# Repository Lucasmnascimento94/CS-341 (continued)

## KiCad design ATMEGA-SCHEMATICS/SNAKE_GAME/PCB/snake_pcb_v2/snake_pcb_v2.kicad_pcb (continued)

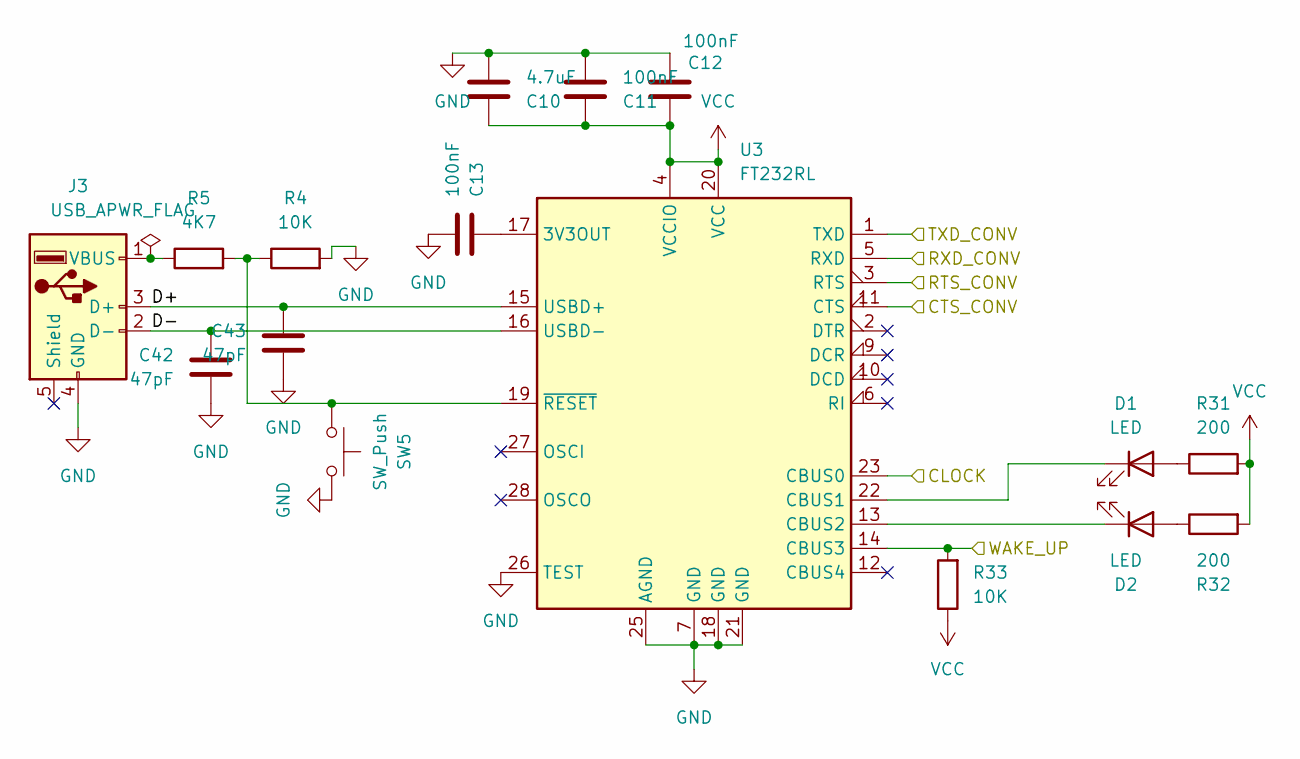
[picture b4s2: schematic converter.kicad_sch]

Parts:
C10: 4.7uF; C_0805_2012Metric
C11, C12, C13: 100nF; C_0402_1005Metric
C42, C43: 47pF; C_0402_1005Metric
D1, D2: LED; LED_0603_1608Metric
J3: USB_A; USB_B_Lumberg_2411_02_Horizontal
R4, R33: 10K; R_0402_1005Metric
R5: 4K7; R_0402_1005Metric
R31, R32: 200; R_0402_1005Metric
SW5: SW_Push; SW_PUSH_1P1T_6x3.5mm_H4.3_APEM_MJTP1243
U3: FT232RL; SSOP-28_5.3x10.2mm_P0.65mm

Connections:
/converter/CLOCK: U3.23 (CBUS0); also elsewhere on the board
/converter/CTS_CONV: U3.11 (CTS); also elsewhere on the board
/converter/D+: C43.1, J3.3 (D+), U3.15 (USBD+)
/converter/D-: C42.1, J3.2 (D-), U3.16 (USBD-)
/converter/RTS_CONV: U3.3 (RTS); also elsewhere on the board
/converter/RXD_CONV: U3.5 (RXD); also elsewhere on the board
/converter/TXD_CONV: U3.1 (TXD); also elsewhere on the board
/converter/WAKE_UP: R33.2, U3.14 (CBUS3); also elsewhere on the board
GND: C10.2, C11.2, C12.2, C13.2, C42.2, C43.2, J3.4 (GND), R4.2, SW5.2, U3.7 (GND), U3.18 (GND), U3.21 (GND), U3.25 (AGND), U3.26 (TEST); also elsewhere on the board
unnamed: D1.2 (A), R31.1
unnamed: D1.1 (K), U3.22 (CBUS1)
unnamed: D2.2 (A), R32.1
unnamed: D2.1 (K), U3.13 (CBUS2)
unnamed: J3.1 (VBUS), R5.1
unnamed: C13.1, U3.17 (3V3OUT)
unnamed: R4.1, R5.2, SW5.1, U3.19 (~RESET)
VCC: C10.1, C11.1, C12.1, R31.2, R32.2, R33.1, U3.4 (VCCIO), U3.20 (VCC); also elsewhere on the board

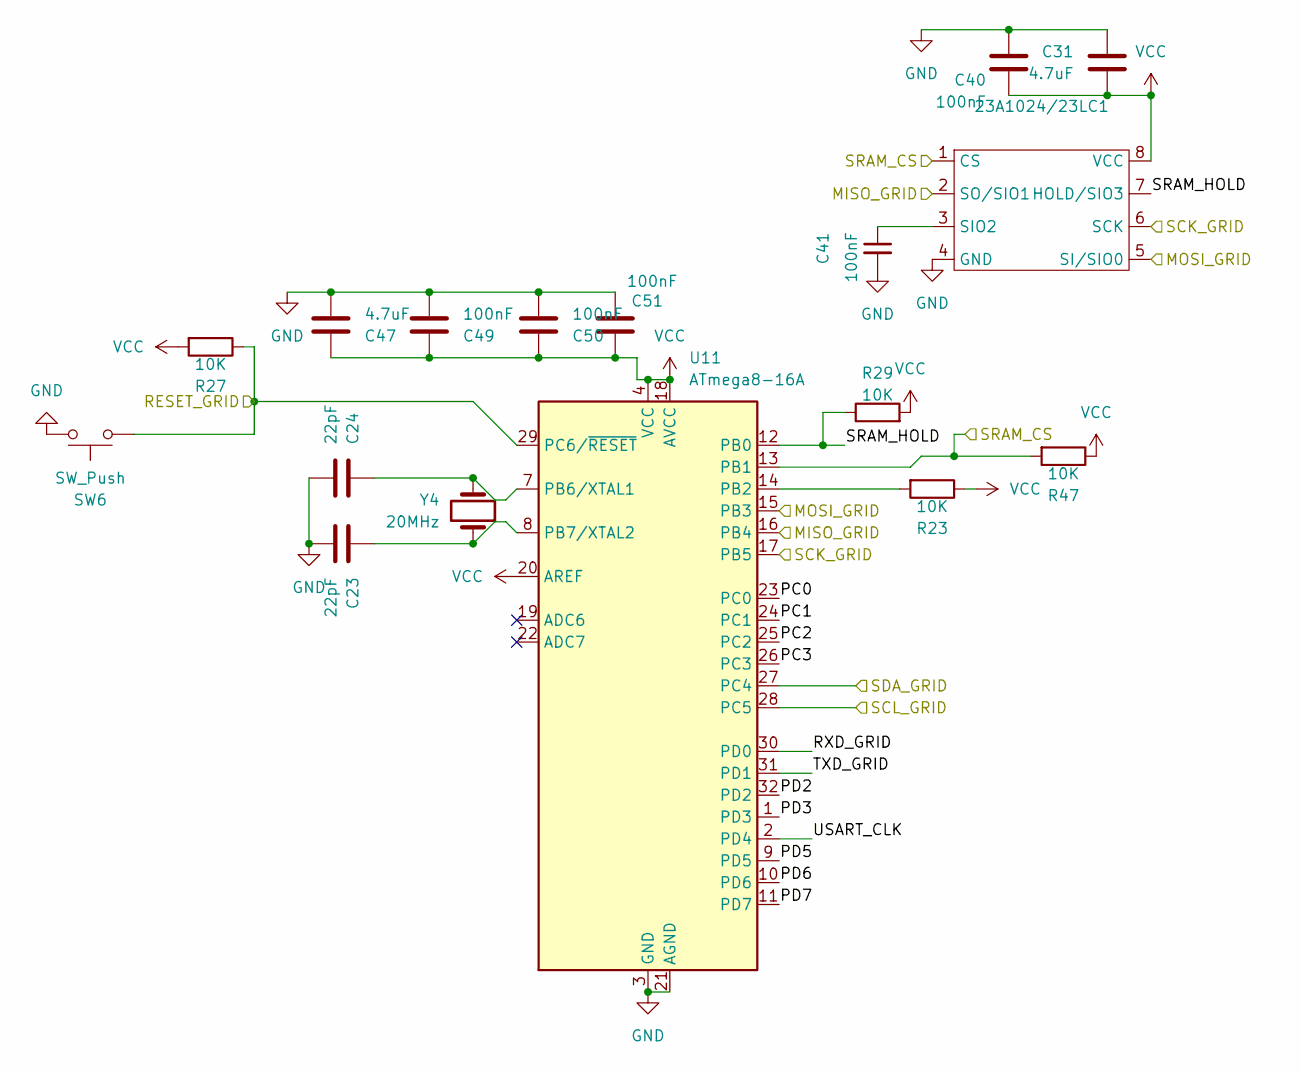
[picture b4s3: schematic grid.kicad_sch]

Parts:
23A1024/23LC1: JEITA_SOIC-8_3.9x4.9mm_P1.27mm
C23, C24: 22pF; C_0402_1005Metric
C31, C47: 4.7uF; C_0805_2012Metric
C40, C41, C49, C50, C51: 100nF; C_0402_1005Metric
R23, R27, R29, R47: 10K; R_0402_1005Metric
SW6: SW_Push; SW_PUSH_1P1T_6x3.5mm_H4.3_APEM_MJTP1243
U11: ATmega8-16A; TQFP-32_7x7mm_P0.8mm
Y4: 20MHz; Crystal_SMD_3225-4Pin_3.2x2.5mm_HandSoldering

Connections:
/game/SCL_GAME: U11.28 (PC5); also elsewhere on the board
/game/SDA_GAME: U11.27 (PC4); also elsewhere on the board
/grid/MISO_GRID: 23A1024/23LC1.2 (SO/SIO1), U11.16 (PB4); also elsewhere on the board
/grid/MOSI_GRID: 23A1024/23LC1.5 (SI/SIO0), U11.15 (PB3); also elsewhere on the board
/grid/PC0: U11.23 (PC0)
/grid/PC1: U11.24 (PC1)
/grid/PC2: U11.25 (PC2)
/grid/PC3: U11.26 (PC3)
/grid/PD2: U11.32 (PD2)
/grid/PD3: U11.1 (PD3)
/grid/PD5: U11.9 (PD5)
/grid/PD6: U11.10 (PD6)
/grid/PD7: U11.11 (PD7)
/grid/RESET_GRID: R27.1, SW6.1, U11.29 (PC6/~RESET); also elsewhere on the board
/grid/RXD_GRID: U11.30 (PD0)
/grid/SCK_GRID: 23A1024/23LC1.6 (SCK), U11.17 (PB5); also elsewhere on the board
/grid/SRAM_CS: 23A1024/23LC1.1 (CS), R47.2, U11.13 (PB1); also elsewhere on the board
/grid/SRAM_HOLD: 23A1024/23LC1.7 (HOLD/SIO3), R29.1, U11.12 (PB0)
/grid/TXD_GRID: U11.31 (PD1)
/grid/USART_CLK: U11.2 (PD4)
GND: 23A1024/23LC1.4 (GND), C23.2, C24.2, C31.1, C40.1, C41.2, C47.2, C49.2, C50.2, C51.2, SW6.2, U11.3 (GND), U11.5 (GND), U11.21 (AGND); also elsewhere on the board
unnamed: 23A1024/23LC1.3 (SIO2), C41.1
unnamed: R23.2, U11.14 (PB2)
unnamed: C24.1, U11.7 (PB6/XTAL1), Y4.2
unnamed: C23.1, U11.8 (PB7/XTAL2), Y4.1
VCC: 23A1024/23LC1.8 (VCC), C31.2, C40.2, C47.1, C49.1, C50.1, C51.1, R23.1, R27.2, R29.2, R47.1, U11.4 (VCC), U11.6 (VCC), U11.18 (AVCC), U11.20 (AREF); also elsewhere on the board

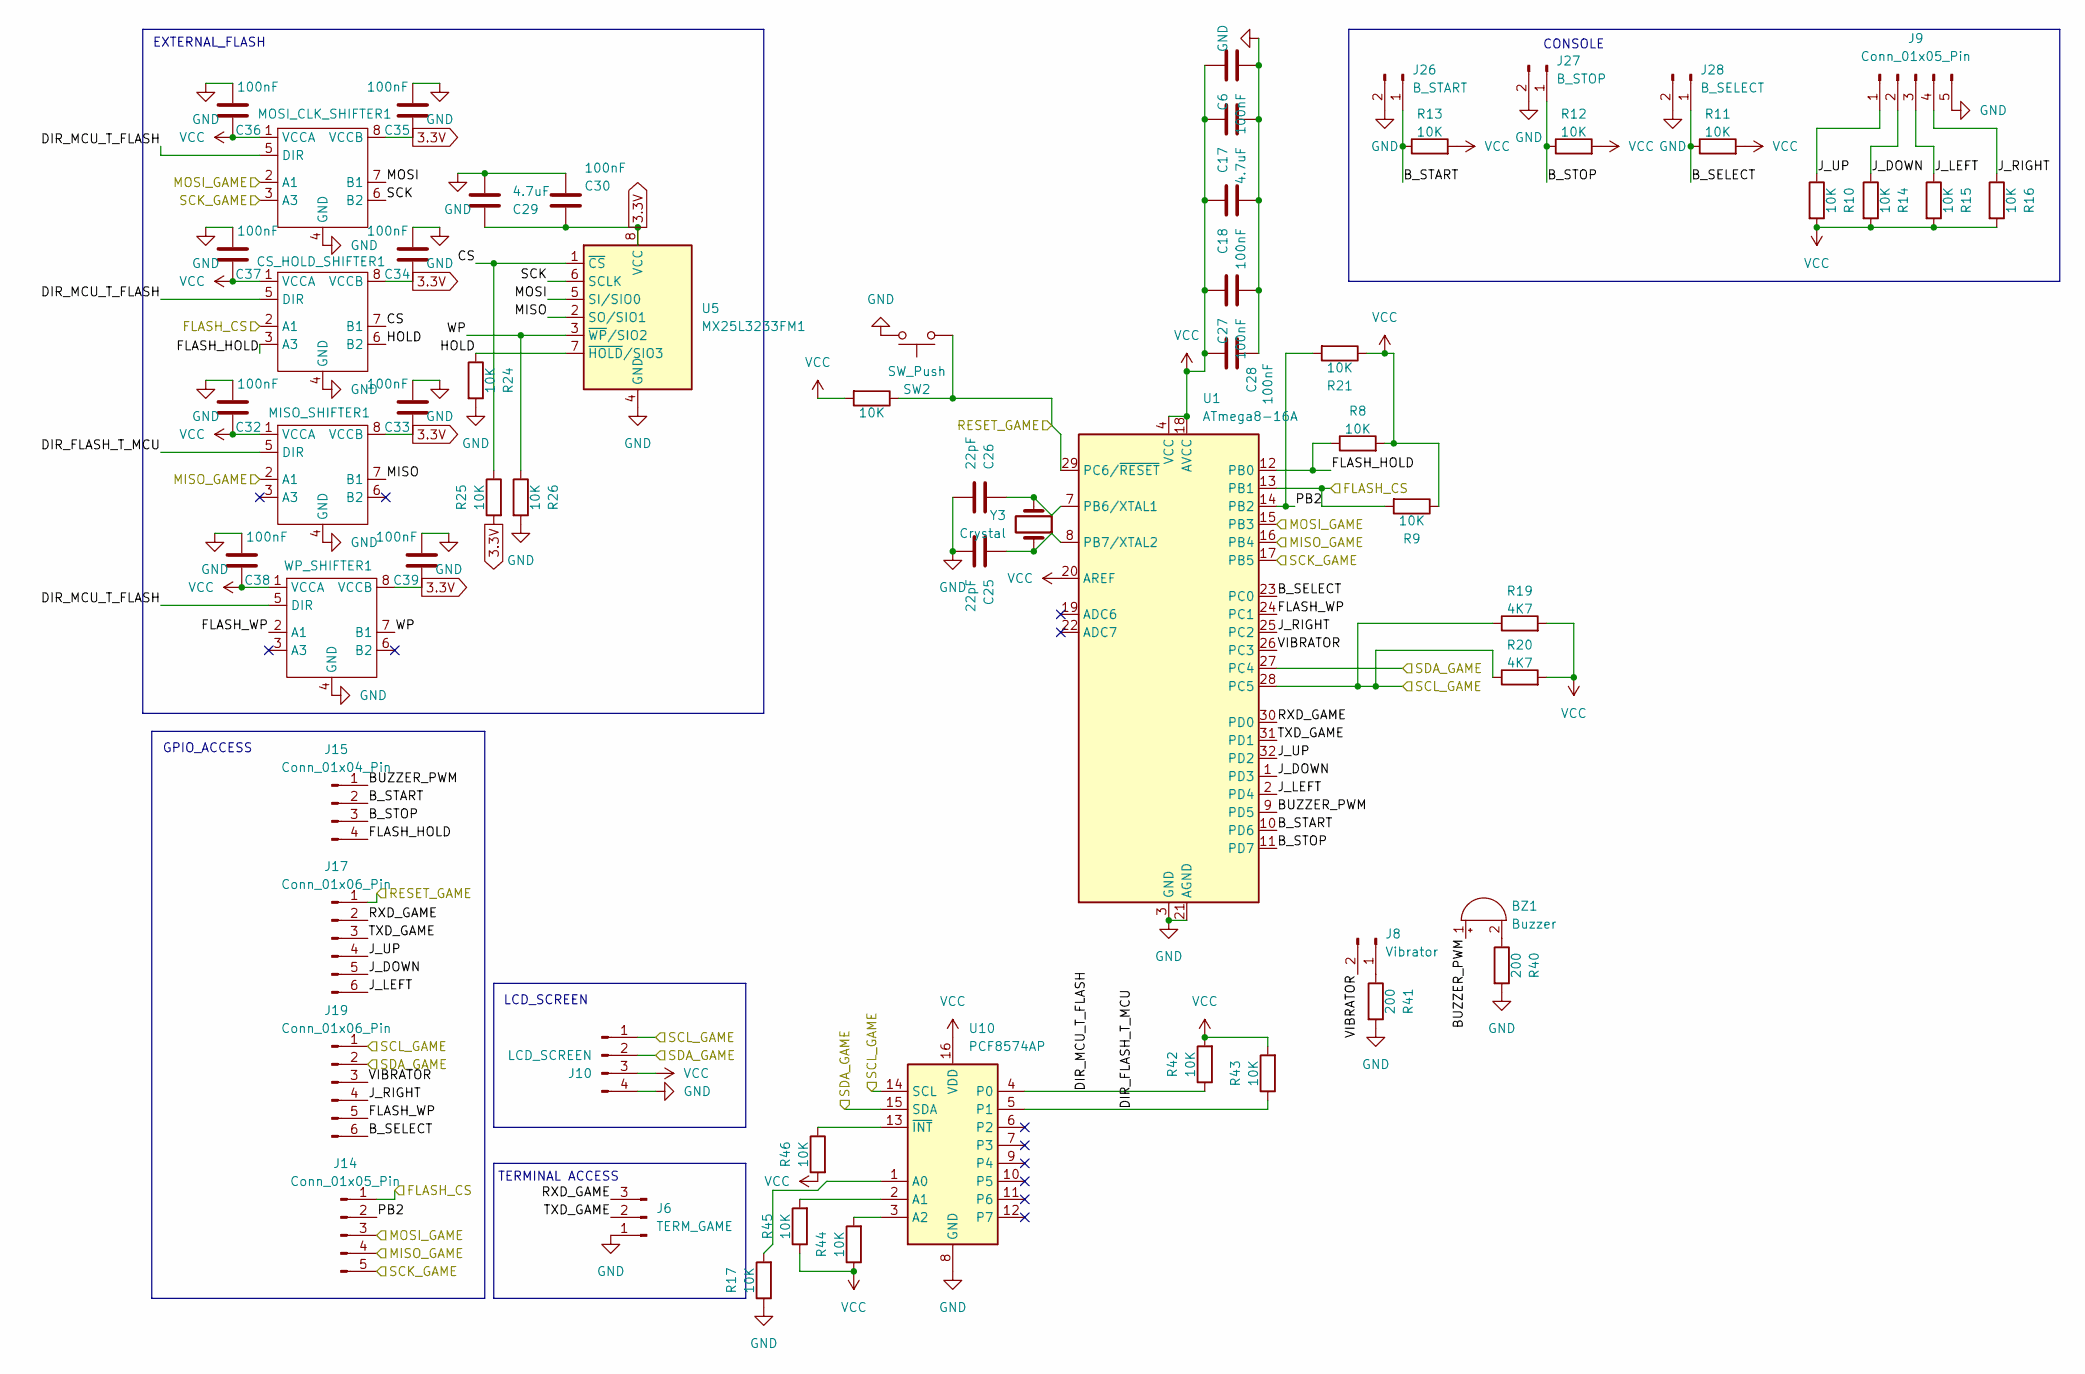
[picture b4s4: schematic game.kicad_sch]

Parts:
BZ1: Buzzer; Buzzer_12x9.5RM7.6
C6, C18, C27, C28, C30, C32, C33, C34, C35, C36, C37, C38, C39: 100nF; C_0402_1005Metric
C17, C29: 4.7uF; C_0805_2012Metric
C25, C26: 22pF; C_0402_1005Metric
CS_HOLD_SHIFTER1: DIP-8_W7.62mm
J6: TERM_GAME; PinSocket_1x03_P2.54mm_Vertical
J8: Vibrator; PinHeader_1x02_P2.54mm_Vertical
J9: Conn_01x05_Pin; PinSocket_1x05_P2.54mm_Vertical
J10: LCD_SCREEN; PinSocket_1x04_P2.54mm_Vertical
J14: Conn_01x05_Pin; PinHeader_1x05_P2.54mm_Vertical
J15: Conn_01x04_Pin; PinHeader_1x04_P2.54mm_Vertical
J17, J19: Conn_01x06_Pin; PinHeader_1x06_P2.54mm_Vertical
J26: B_START; PinHeader_1x02_P2.54mm_Vertical
J27: B_STOP; PinHeader_1x02_P2.54mm_Vertical
J28: B_SELECT; PinHeader_1x02_P2.54mm_Vertical
MISO_SHIFTER1: DIP-8_W7.62mm
MOSI_CLK_SHIFTER1: DIP-8_W7.62mm
R7, R8, R9, R10, R11, R12, R13, R14, R15, R16, R17, R21, R24, R25, R26, R42, R43, R44, R45, R46: 10K; R_0402_1005Metric
R19, R20: 4K7; R_0402_1005Metric
R40, R41: 200; R_0402_1005Metric
SW2: SW_Push; SW_PUSH_1P1T_6x3.5mm_H4.3_APEM_MJTP1243
U1: ATmega8-16A; TQFP-32_7x7mm_P0.8mm
U5: MX25L3233FM1; JEITA_SOIC-8_3.9x4.9mm_P1.27mm
U10: PCF8574AP; DIP-16_W7.62mm
WP_SHIFTER1: DIP-8_W7.62mm
Y3: Crystal; Crystal_SMD_3225-4Pin_3.2x2.5mm_HandSoldering

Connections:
3.3V: C29.1, C30.1, C33.1, C34.1, C35.1, C39.1, CS_HOLD_SHIFTER1.8 (VCCB), MISO_SHIFTER1.8 (VCCB), MOSI_CLK_SHIFTER1.8 (VCCB), R25.2, U5.8 (VCC), WP_SHIFTER1.8 (VCCB); also elsewhere on the board
/game/BUZZER_PWM: BZ1.1 (+), J15.1, U1.9 (PD5)
/game/B_SELECT: J19.6, J28.1, R11.1, U1.23 (PC0)
/game/B_START: J15.2, J26.1, R13.1, U1.10 (PD6)
/game/B_STOP: J15.3, J27.1, R12.1, U1.11 (PD7)
/game/CS: CS_HOLD_SHIFTER1.7 (B1), R25.1, U5.1 (~CS)
/game/DIR_FLASH_T_MCU: MISO_SHIFTER1.5 (DIR), R43.1, U10.5 (P1)
/game/DIR_MCU_T_FLASH: CS_HOLD_SHIFTER1.5 (DIR), MOSI_CLK_SHIFTER1.5 (DIR), R42.1, U10.4 (P0), WP_SHIFTER1.5 (DIR)
/game/FLASH_CS: CS_HOLD_SHIFTER1.2 (A1), J14.1, R9.2, U1.13 (PB1); also elsewhere on the board
/game/FLASH_HOLD: CS_HOLD_SHIFTER1.3 (A3), J15.4, R8.1, U1.12 (PB0)
/game/FLASH_WP: J19.5, U1.24 (PC1), WP_SHIFTER1.2 (A1)
/game/HOLD: CS_HOLD_SHIFTER1.6 (B2), R24.1, U5.7 (~HOLD/SIO3)
/game/J_DOWN: J9.2, J17.5, R14.1, U1.1 (PD3)
/game/J_LEFT: J9.3, J17.6, R15.1, U1.2 (PD4)
/game/J_RIGHT: J9.4, J19.4, R16.1, U1.25 (PC2)
/game/J_UP: J9.1, J17.4, R10.1, U1.32 (PD2)
/game/MISO: MISO_SHIFTER1.7 (B1), U5.2 (SO/SIO1)
/game/MISO_GAME: J14.4, MISO_SHIFTER1.2 (A1), U1.16 (PB4); also elsewhere on the board
/game/MOSI: MOSI_CLK_SHIFTER1.7 (B1), U5.5 (SI/SIO0)
/game/MOSI_GAME: J14.3, MOSI_CLK_SHIFTER1.2 (A1), U1.15 (PB3); also elsewhere on the board
/game/PB2: J14.2, R21.2, U1.14 (PB2)
/game/RESET_GAME: J17.1, R7.1, SW2.1, U1.29 (PC6/~RESET); also elsewhere on the board
/game/RXD_GAME: J6.3, J17.2, U1.30 (PD0)
/game/SCK: MOSI_CLK_SHIFTER1.6 (B2), U5.6 (SCLK)
/game/SCK_GAME: J14.5, MOSI_CLK_SHIFTER1.3 (A3), U1.17 (PB5); also elsewhere on the board
/game/SCL_GAME: J10.1, J19.1, R19.1, R20.1, U1.28 (PC5), U10.14 (SCL); also elsewhere on the board
/game/SDA_GAME: J10.2, J19.2, U1.27 (PC4), U10.15 (SDA); also elsewhere on the board
/game/TXD_GAME: J6.2, J17.3, U1.31 (PD1)
/game/VIBRATOR: J8.2, J19.3, U1.26 (PC3)
/game/WP: R26.1, U5.3 (~WP/SIO2), WP_SHIFTER1.7 (B1)
GND: C6.2, C17.2, C18.2, C25.2, C26.2, C27.2, C28.2, C29.2, C30.2, C32.2, C33.2, C34.2, C35.2, C36.2, C37.2, C38.2, C39.2, CS_HOLD_SHIFTER1.4 (GND), J6.1, J9.5, J10.4, J26.2, J27.2, J28.2, MISO_SHIFTER1.4 (GND), MOSI_CLK_SHIFTER1.4 (GND), R17.1, R24.2, R26.2, R40.2, R41.2, SW2.2, U1.3 (GND), U1.5 (GND), U1.21 (AGND), U5.4 (GND), U10.8 (GND), WP_SHIFTER1.4 (GND); also elsewhere on the board
unnamed: BZ1.2 (-), R40.1
unnamed: J8.1, R41.1
unnamed: C26.1, U1.7 (PB6/XTAL1), Y3.2
unnamed: C25.1, U1.8 (PB7/XTAL2), Y3.1
unnamed: R17.2, U10.1 (A0)
unnamed: R45.2, U10.2 (A1)
unnamed: R44.2, U10.3 (A2)
unnamed: R46.1, U10.13 (~INT)
VCC: C6.1, C17.1, C18.1, C27.1, C28.1, C32.1, C36.1, C37.1, C38.1, CS_HOLD_SHIFTER1.1 (VCCA), J10.3, MISO_SHIFTER1.1 (VCCA), MOSI_CLK_SHIFTER1.1 (VCCA), R7.2, R8.2, R9.1, R10.2, R11.2, R12.2, R13.2, R14.2, R15.2, R16.2, R19.2, R20.2, R21.1, R42.2, R43.2, R44.1, R45.1, R46.2, U1.4 (VCC), U1.6 (VCC), U1.18 (AVCC), U1.20 (AREF), U10.16 (VDD), WP_SHIFTER1.1 (VCCA); also elsewhere on the board

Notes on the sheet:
TERMINAL ACCESS
GPIO_ACCESS
CONSOLE
EXTERNAL_FLASH
LCD_SCREEN

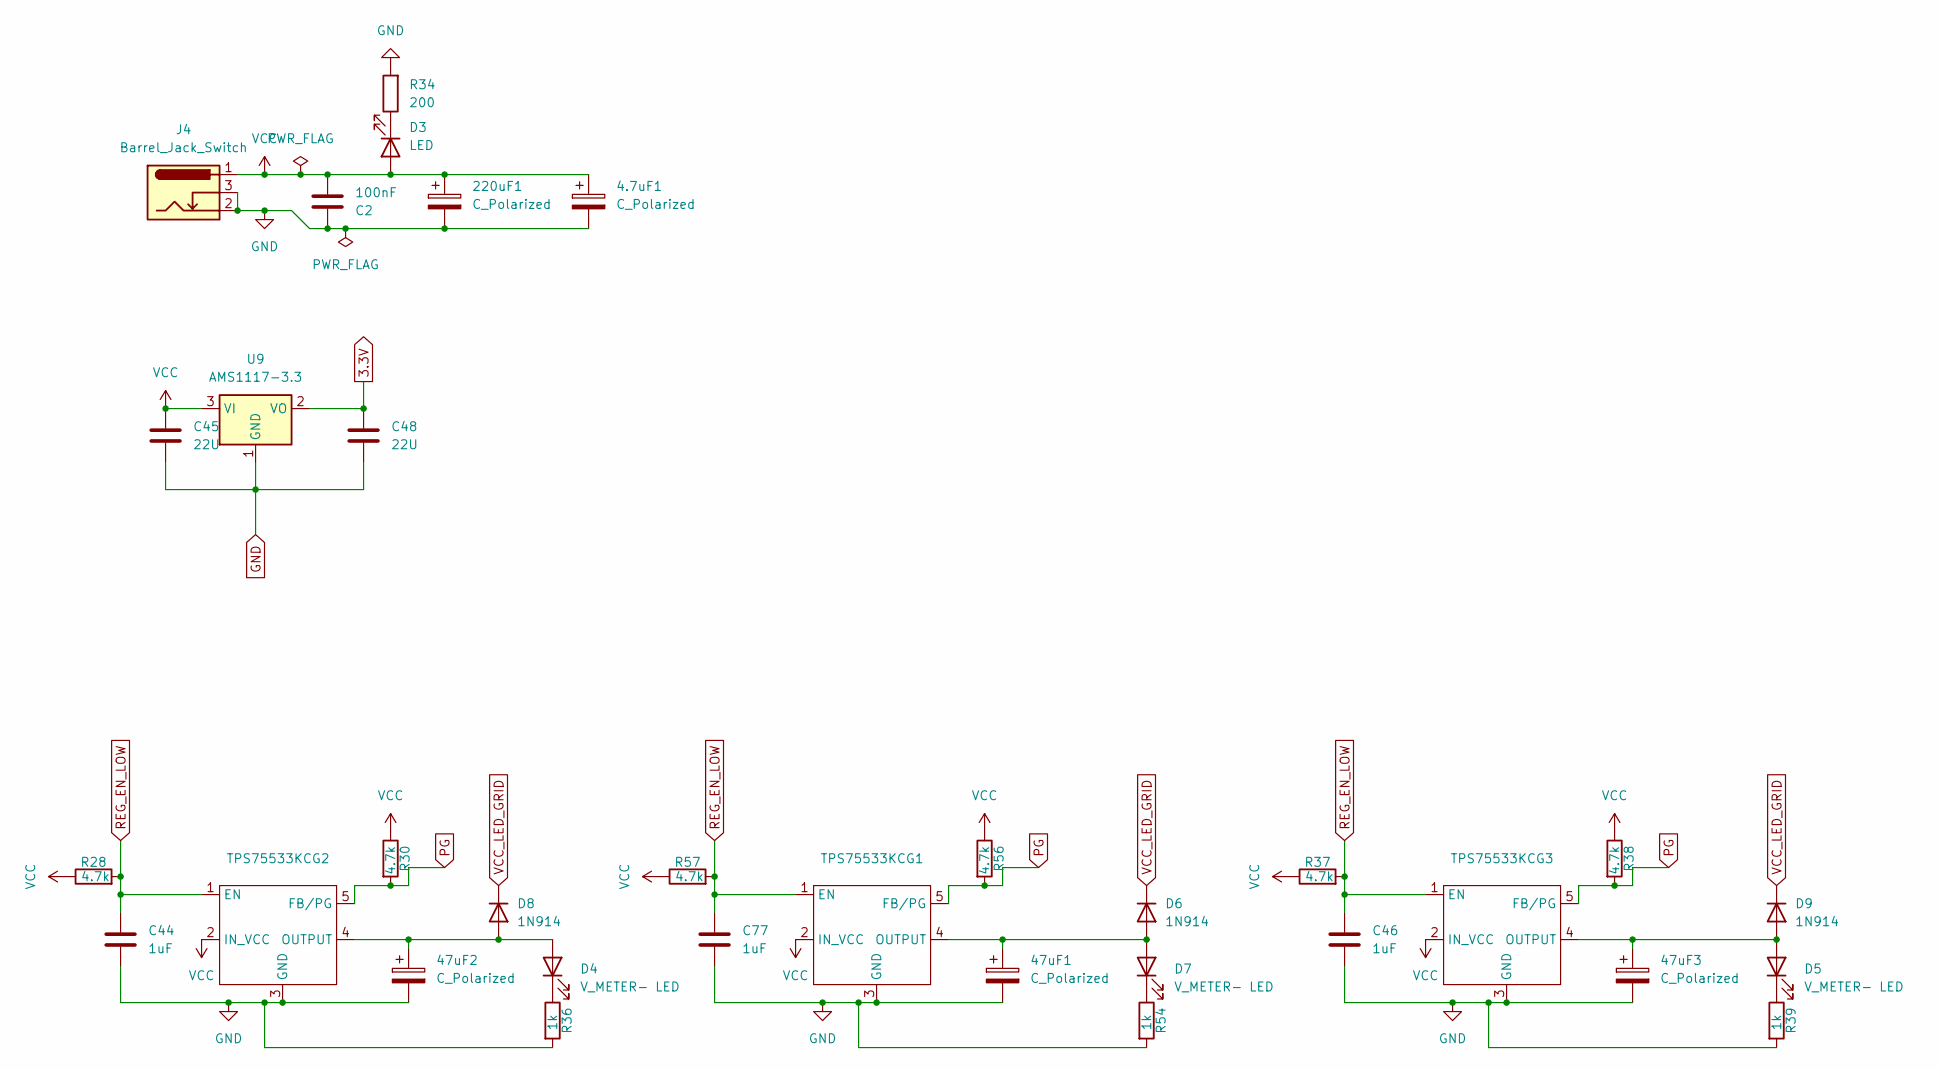
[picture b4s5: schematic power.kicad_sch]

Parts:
4.7uF1, 47uF1, 47uF2, 47uF3, 220uF1: C_Polarized; C_Disc_D3.0mm_W1.6mm_P2.50mm
C2: 100nF; C_0402_1005Metric
C44, C46, C77: 1uF; C_0805_2012Metric
C45, C48: 22U; C_0805_2012Metric
D3: LED; LED_0603_1608Metric
D4, D5, D7: V_METER- LED; LED_0603_1608Metric
D6, D8, D9: 1N914; D_DO-35_SOD27_P7.62mm_Horizontal
J4: Barrel_Jack_Switch; BarrelJack_Horizontal
R28, R30, R37, R38, R56, R57: 4.7k; R_0402_1005Metric
R34: 200; R_0402_1005Metric
R36, R39, R54: 1k; R_0402_1005Metric
TPS75533KCG1, TPS75533KCG2, TPS75533KCG3: TO-220-5_Vertical
U9: AMS1117-3.3; SOT-223-3_TabPin2

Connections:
3.3V: C48.1, U9.2 (VO); also elsewhere on the board
GND: 4.7uF1.2, 47uF1.2, 47uF2.2, 47uF3.2, 220uF1.2, C2.1, C44.2, C45.2, C46.2, C48.2, C77.2, J4.2, J4.3, R34.2, R36.2, R39.2, R54.2, TPS75533KCG1.3 (GND), TPS75533KCG2.3 (GND), TPS75533KCG3.3 (GND), U9.1 (GND); also elsewhere on the board
unnamed: D3.1 (K), R34.1
unnamed: 47uF2.1, D4.2 (A), D8.2 (A), TPS75533KCG2.4 (OUTPUT)
unnamed: D4.1 (K), R36.1
unnamed: 47uF3.1, D5.2 (A), D9.2 (A), TPS75533KCG3.4 (OUTPUT)
unnamed: D5.1 (K), R39.1
unnamed: 47uF1.1, D6.2 (A), D7.2 (A), TPS75533KCG1.4 (OUTPUT)
unnamed: D7.1 (K), R54.1
PG: R30.2, R38.2, R56.2, TPS75533KCG1.5 (FB/PG), TPS75533KCG2.5 (FB/PG), TPS75533KCG3.5 (FB/PG)
REG_EN_LOW: C44.1, C46.1, C77.1, R28.2, R37.2, R57.2, TPS75533KCG1.1 (EN), TPS75533KCG2.1 (EN), TPS75533KCG3.1 (EN)
VCC: 4.7uF1.1, 220uF1.1, C2.2, C45.1, D3.2 (A), J4.1, R28.1, R30.1, R37.1, R38.1, R56.1, R57.1, TPS75533KCG1.2 (IN_VCC), TPS75533KCG2.2 (IN_VCC), TPS75533KCG3.2 (IN_VCC), U9.3 (VI); also elsewhere on the board
VCC_LED_GRID: D6.1 (K), D8.1 (K), D9.1 (K)

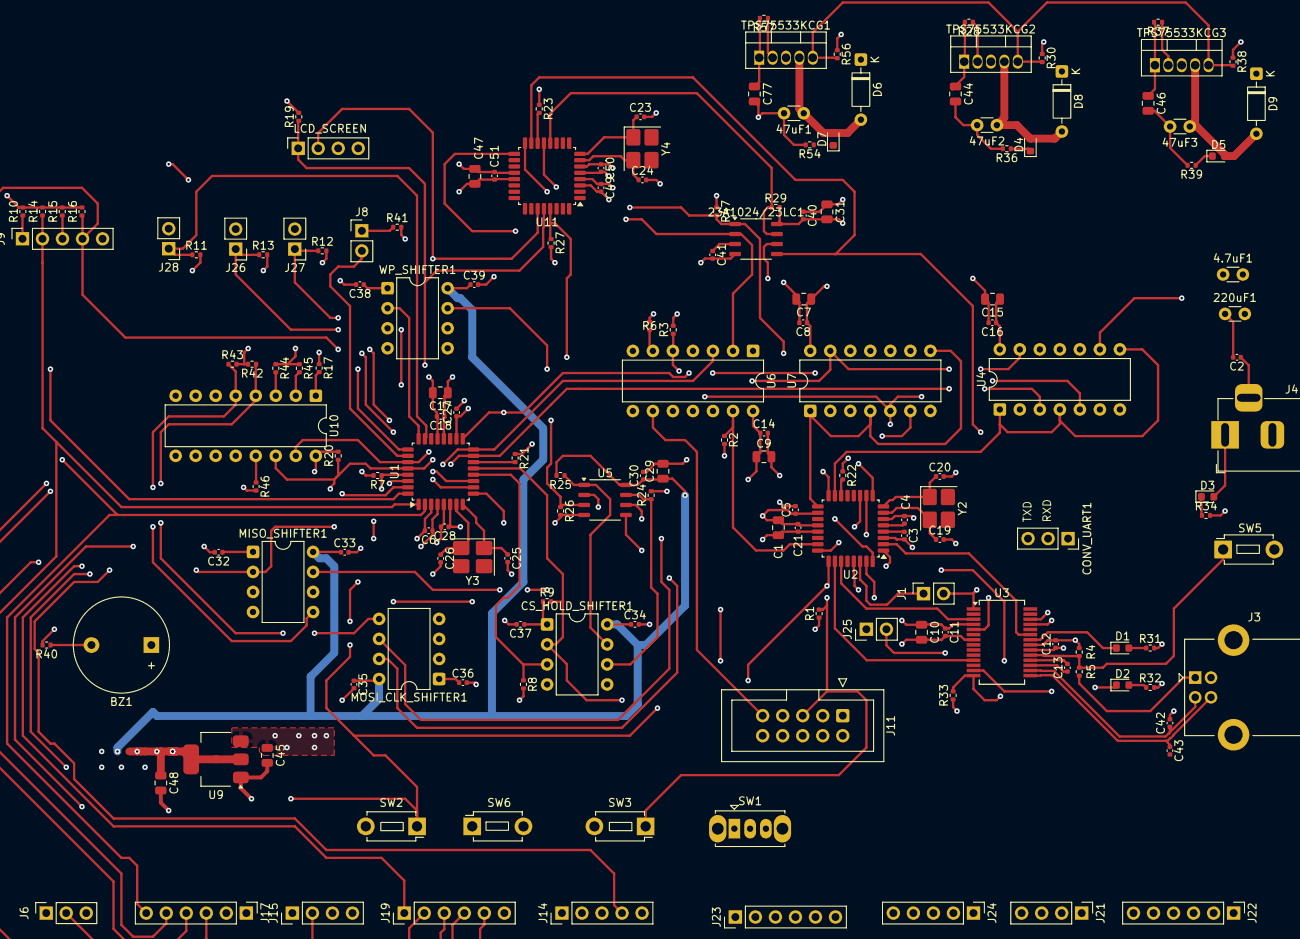
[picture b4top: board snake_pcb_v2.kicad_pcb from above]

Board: 4 copper layers, 161 parts (0 on the bottom side), 93 nets.

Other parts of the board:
LCD_SCREEN: LCD_SCREEN; PinSocket_1x04_P2.54mm_Vertical

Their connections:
/game/SCL_GAME: LCD_SCREEN.1; also elsewhere on the board
/game/SDA_GAME: LCD_SCREEN.2; also elsewhere on the board
GND: LCD_SCREEN.4; also elsewhere on the board
VCC: LCD_SCREEN.3; also elsewhere on the board

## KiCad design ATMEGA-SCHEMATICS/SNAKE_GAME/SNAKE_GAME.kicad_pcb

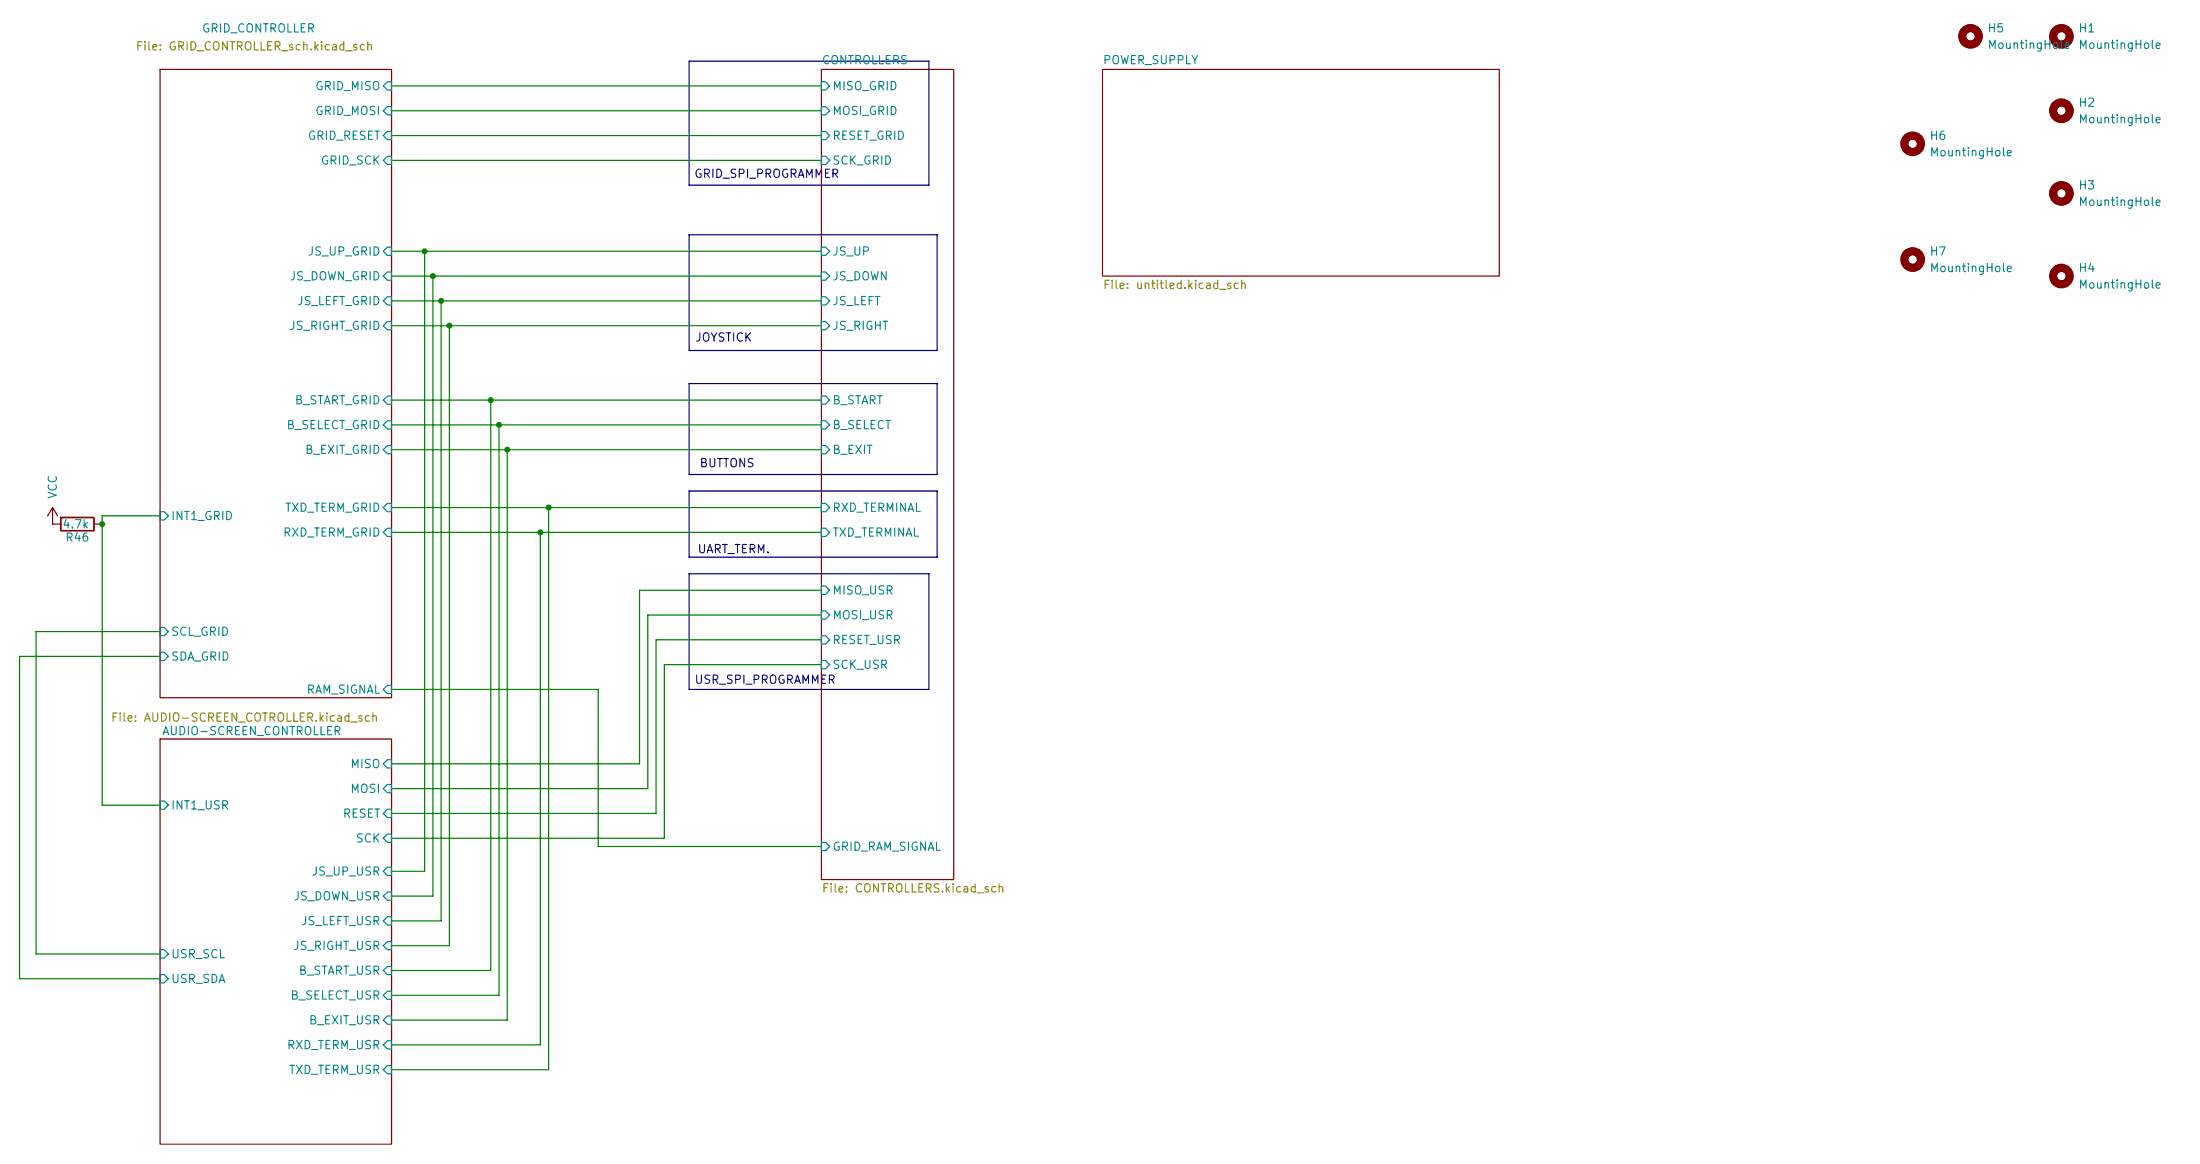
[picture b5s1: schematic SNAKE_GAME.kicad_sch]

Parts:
H1, H2, H3, H4, H5, H6, H7: MountingHole; MountingHole_3.2mm_M3
R46: 4.7k; R_Axial_DIN0207_L6.3mm_D2.5mm_P10.16mm_Horizontal

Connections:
/AUDIO-SCREEN_CONTROLLER/INT1_USR: R46.1; also elsewhere on the board
VCC: R46.2; also elsewhere on the board

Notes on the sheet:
BUTTONS
JOYSTICK
USR_SPI_PROGRAMMER
UART_TERM.
GRID_SPI_PROGRAMMER

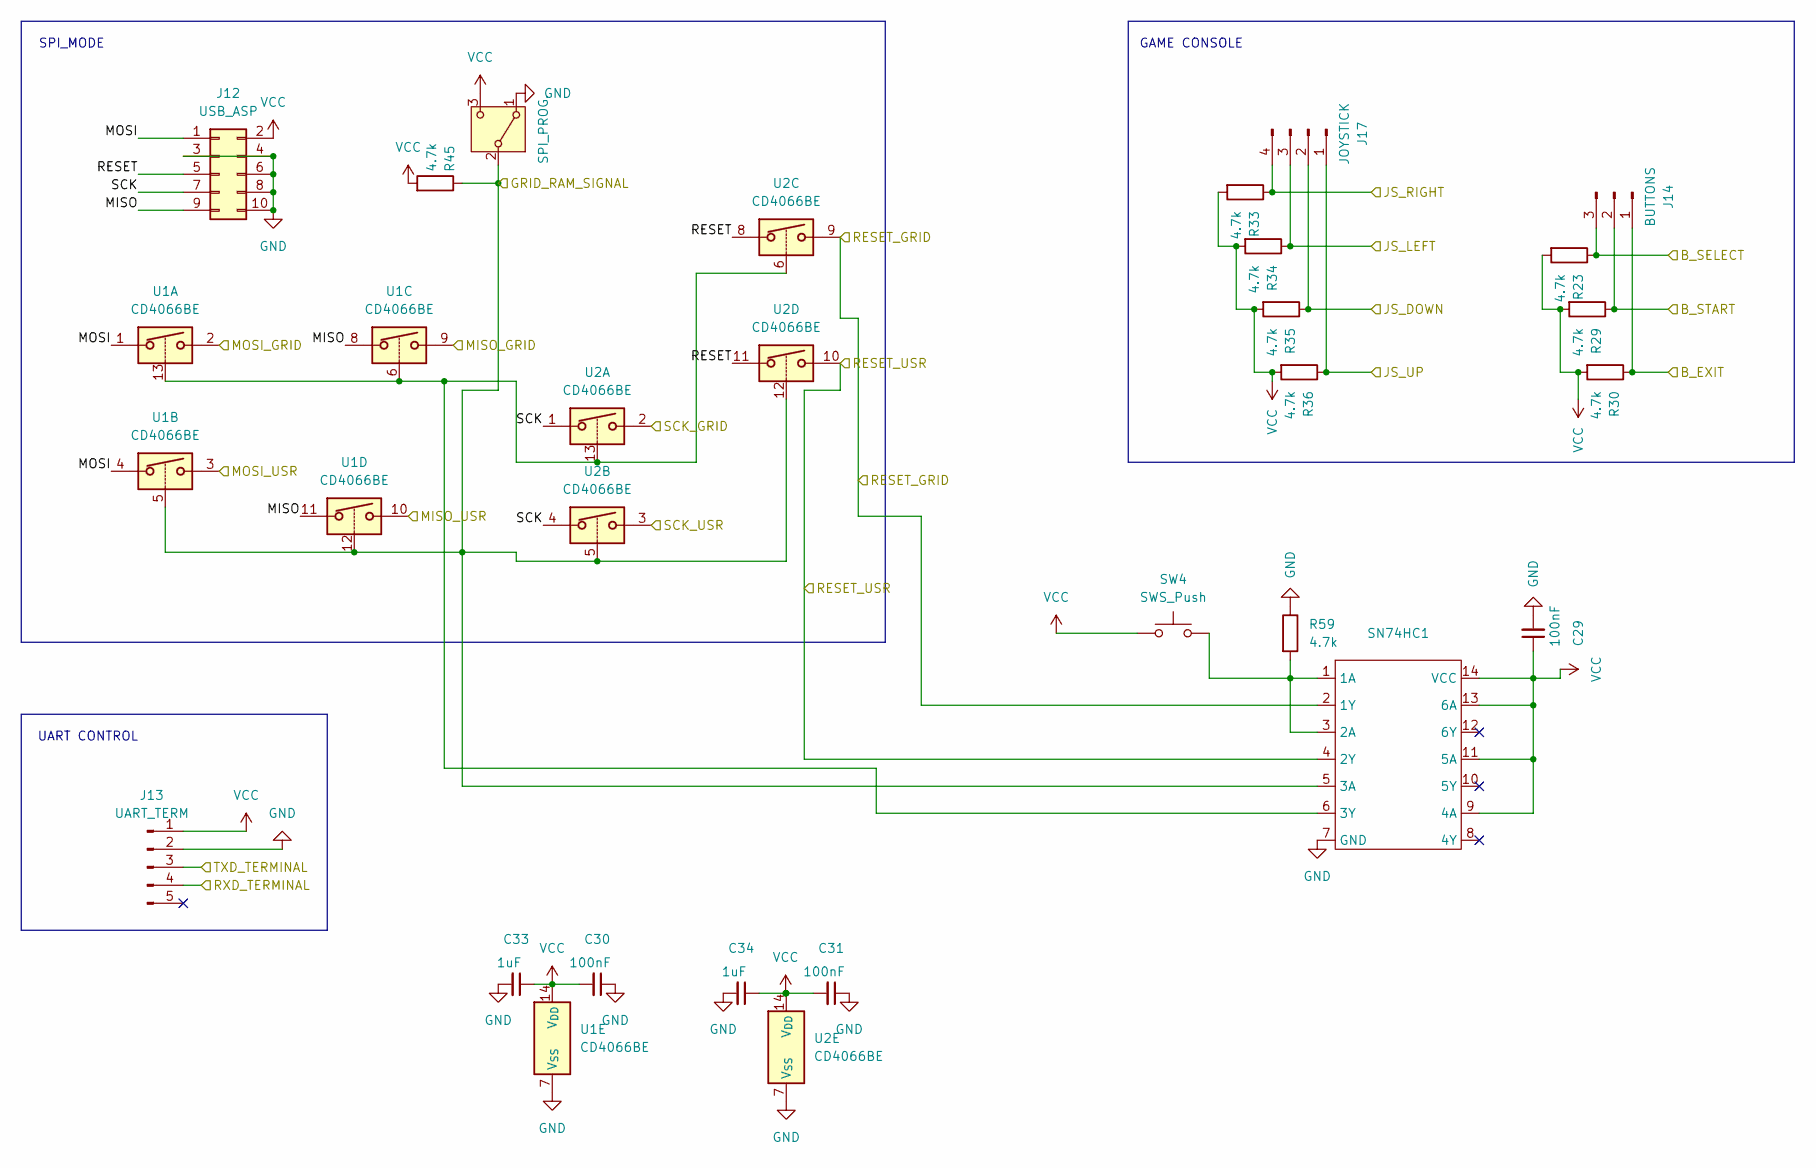
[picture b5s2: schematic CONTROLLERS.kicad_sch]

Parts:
C29, C30, C31: 100nF; C_Disc_D7.5mm_W5.0mm_P5.00mm
C33, C34: 1uF; C_Disc_D7.5mm_W5.0mm_P5.00mm
J12: USB_ASP; IDC-Header_2x05_P2.54mm_Vertical
J13: UART_TERM; PinSocket_1x04_P2.54mm_Vertical
J14: BUTTONS; TerminalBlock_MaiXu_MX126-5.0-03P_1x03_P5.00mm
J17: JOYSTICK; TerminalBlock_MaiXu_MX126-5.0-04P_1x04_P5.00mm
R23, R29, R30, R33, R34, R35, R36, R45, R59: 4.7k; R_Axial_DIN0207_L6.3mm_D2.5mm_P10.16mm_Horizontal
SN74HC1: CERDIP-14_W7.62mm_SideBrazed_Socket
SW4: SWS_Push; SW_PUSH_6mm
SW6: SPI_PROG.; SW_Slide_SPDT_Straight_CK_OS102011MS2Q
U1, U2: CD4066BE; DIP-14_W7.62mm

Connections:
/AUDIO-SCREEN_CONTROLLER/B_EXIT_USR: J14.1, R30.1; also elsewhere on the board
/AUDIO-SCREEN_CONTROLLER/B_SELECT_USR: J14.3, R23.1; also elsewhere on the board
/AUDIO-SCREEN_CONTROLLER/B_START_USR: J14.2, R29.1; also elsewhere on the board
/AUDIO-SCREEN_CONTROLLER/JS_DOWN_USR: J17.2, R35.1; also elsewhere on the board
/AUDIO-SCREEN_CONTROLLER/JS_LEFT_USR: J17.3, R34.1; also elsewhere on the board
/AUDIO-SCREEN_CONTROLLER/JS_RIGHT_USR: J17.4, R33.1; also elsewhere on the board
/AUDIO-SCREEN_CONTROLLER/JS_UP_USR: J17.1, R36.1; also elsewhere on the board
/AUDIO-SCREEN_CONTROLLER/MISO: U1.10; also elsewhere on the board
/AUDIO-SCREEN_CONTROLLER/MOSI: U1.3; also elsewhere on the board
/AUDIO-SCREEN_CONTROLLER/RESET: SN74HC1.4 (2Y), U2.10; also elsewhere on the board
/AUDIO-SCREEN_CONTROLLER/RXD_TERM_USR: J13.3; also elsewhere on the board
/AUDIO-SCREEN_CONTROLLER/SCK: U2.3; also elsewhere on the board
/AUDIO-SCREEN_CONTROLLER/TXD_TERM_USR: J13.4; also elsewhere on the board
/CONTROLLERS/GRID_RAM_SIGNAL: R45.1, SN74HC1.5 (3A), SW6.2 (B), U1.5, U1.12, U2.5, U2.12; also elsewhere on the board
/CONTROLLERS/MISO: J12.9, U1.8, U1.11
/CONTROLLERS/MISO_GRID: U1.9; also elsewhere on the board
/CONTROLLERS/MOSI: J12.1, U1.1, U1.4
/CONTROLLERS/MOSI_GRID: U1.2; also elsewhere on the board
/CONTROLLERS/RESET: J12.5, U2.8, U2.11
/CONTROLLERS/RESET_GRID: SN74HC1.2 (1Y), U2.9; also elsewhere on the board
/CONTROLLERS/SCK: J12.7, U2.1, U2.4
/CONTROLLERS/SCK_GRID: U2.2; also elsewhere on the board
GND: C29.2, C30.1, C31.1, C33.2, C34.2, J12.3, J12.4, J12.6, J12.8, J12.10, J13.2, R59.1, SN74HC1.7 (GND), SW6.1 (A), U1.7 (V_{SS}), U2.7 (V_{SS}); also elsewhere on the board
unnamed: R59.2, SN74HC1.1 (1A), SN74HC1.3 (2A), SW4.1
unnamed: SN74HC1.6 (3Y), U1.6, U1.13, U2.6, U2.13
VCC: C29.1, C30.2, C31.2, C33.1, C34.1, J12.2, J13.1, R23.2, R29.2, R30.2, R33.2, R34.2, R35.2, R36.2, R45.2, SN74HC1.9 (4A), SN74HC1.11 (5A), SN74HC1.13 (6A), SN74HC1.14 (VCC), SW4.2, SW6.3 (C), U1.14 (V_{DD}), U2.14 (V_{DD}); also elsewhere on the board

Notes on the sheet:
UART CONTROL
GAME CONSOLE
SPI_MODE
